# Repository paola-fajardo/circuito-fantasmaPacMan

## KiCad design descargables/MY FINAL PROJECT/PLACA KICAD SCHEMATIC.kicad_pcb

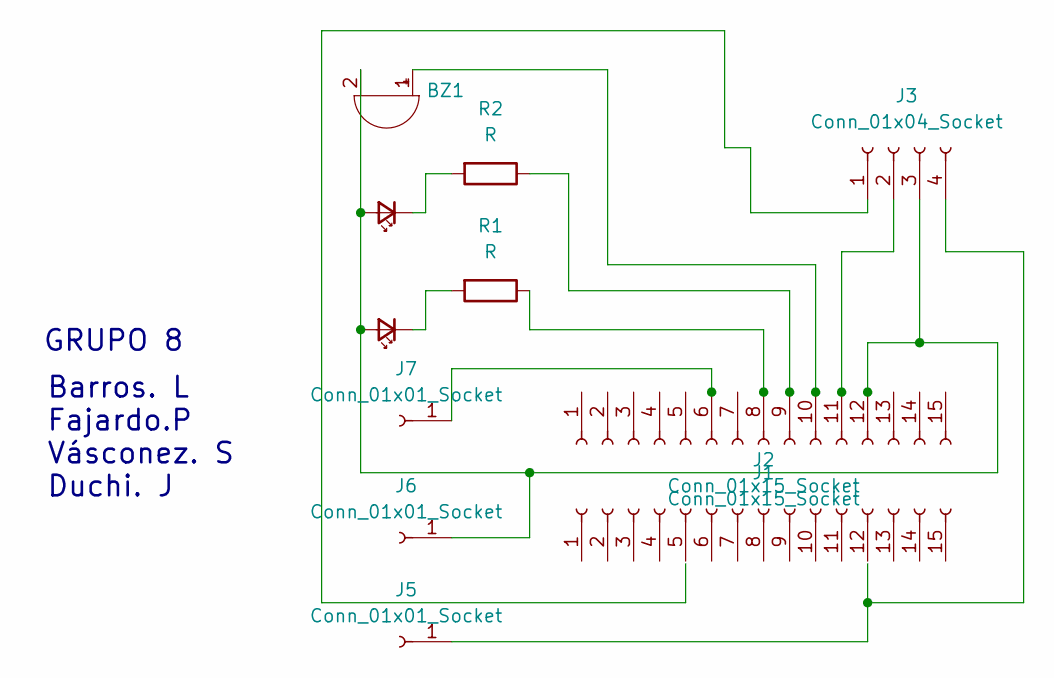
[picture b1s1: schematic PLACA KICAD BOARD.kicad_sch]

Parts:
BZ1: Buzzer; Buzzer_12x9.5RM7.6
D4, D5: LED_Small; LED_D5.0mm
J1, J2: Conn_01x15_Socket; PinSocket_1x15_P2.54mm_Vertical
J3: Conn_01x04_Socket; PinSocket_1x04_P2.54mm_Vertical
J5, J6, J7: Conn_01x01_Socket; PinSocket_1x01_P2.54mm_Vertical
R1, R2: R; R_Axial_DIN0207_L6.3mm_D2.5mm_P10.16mm_Horizontal

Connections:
unnamed: BZ1.1 (+), J1.10
unnamed: BZ1.2 (-), D4.2 (A), D5.2 (A), J1.12, J3.3, J6.1 (Pin_1_1)
unnamed: D4.1 (K), R1.2
unnamed: D5.1 (K), R2.2
unnamed: J1.6, J7.1 (Pin_1_1)
unnamed: J1.8, R1.1
unnamed: J1.9, R2.1
unnamed: J1.11, J3.2
unnamed: J3.4, J5.1 (Pin_1_1)

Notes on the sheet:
GRUPO 8
Barros. L Fajardo.P Vásconez. S Duchi. J

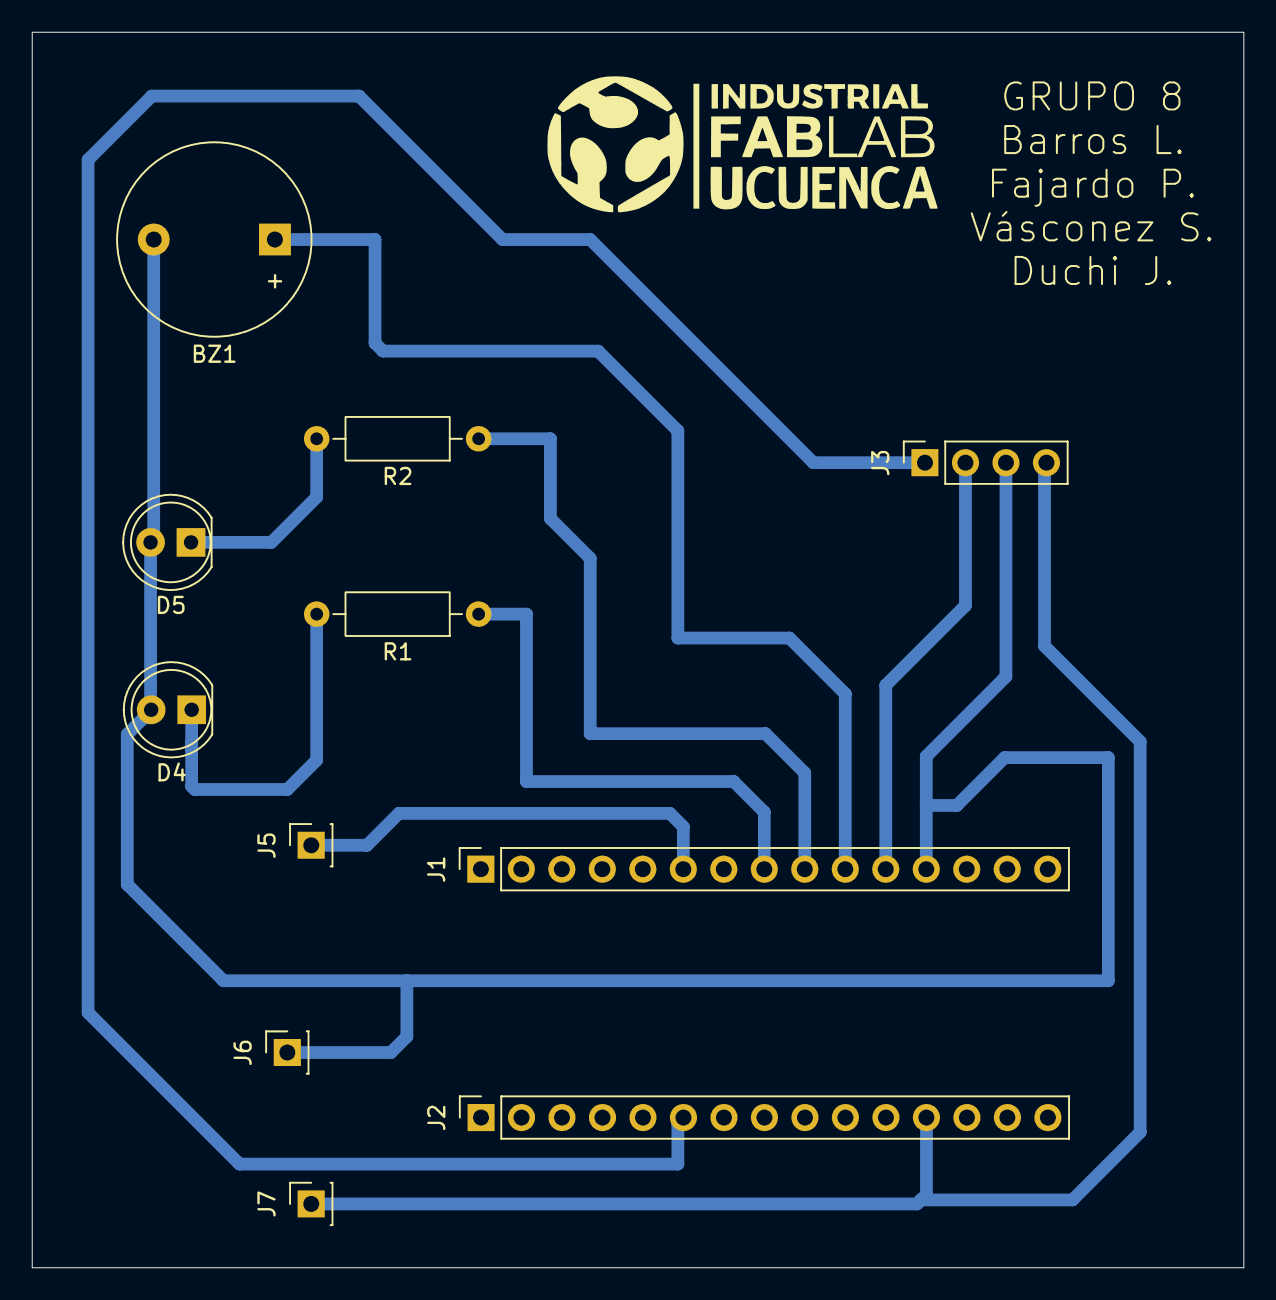
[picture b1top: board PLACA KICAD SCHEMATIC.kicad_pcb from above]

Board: 2 copper layers, 76.0 x 77.5 mm, 11 parts (0 on the bottom side), 9 nets.

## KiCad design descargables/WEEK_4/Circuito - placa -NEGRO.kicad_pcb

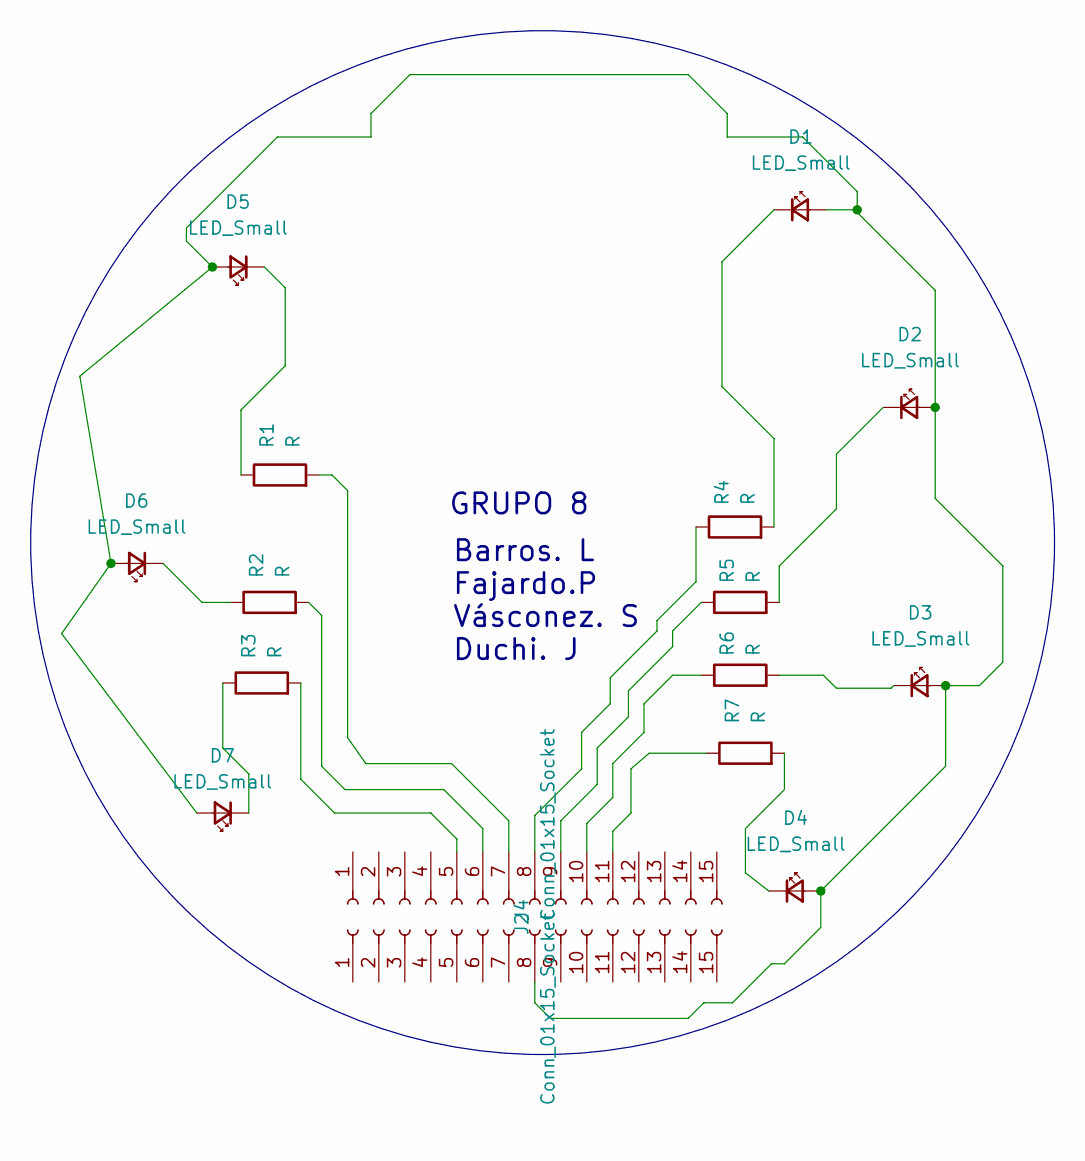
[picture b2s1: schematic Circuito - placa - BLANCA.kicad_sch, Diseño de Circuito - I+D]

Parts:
D1, D2, D3, D4, D5, D6, D7: LED_Small; LED_D5.0mm
J2, J4: Conn_01x15_Socket; PinSocket_1x15_P2.54mm_Vertical
R1, R2, R3, R4, R5, R6, R7: R; R_Axial_DIN0207_L6.3mm_D2.5mm_P10.16mm_Horizontal

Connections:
unnamed: D1.2 (A), D2.2 (A), D3.2 (A), D4.2 (A), D5.2 (A), D6.2 (A), D7.2 (A), J4.8 (Pin_8_8)
unnamed: D1.1 (K), R4.2
unnamed: D2.1 (K), R5.2
unnamed: D3.1 (K), R6.2
unnamed: D4.1 (K), R7.2
unnamed: D5.1 (K), R1.1
unnamed: D6.1 (K), R2.1
unnamed: D7.1 (K), R3.1
unnamed: J2.5, R3.2
unnamed: J2.6, R2.2
unnamed: J2.7, R1.2
unnamed: J2.8, R4.1
unnamed: J2.9, R5.1
unnamed: J2.10, R6.1
unnamed: J2.11, R7.1

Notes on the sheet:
GRUPO 8
Barros. L Fajardo.P Vásconez. S Duchi. J

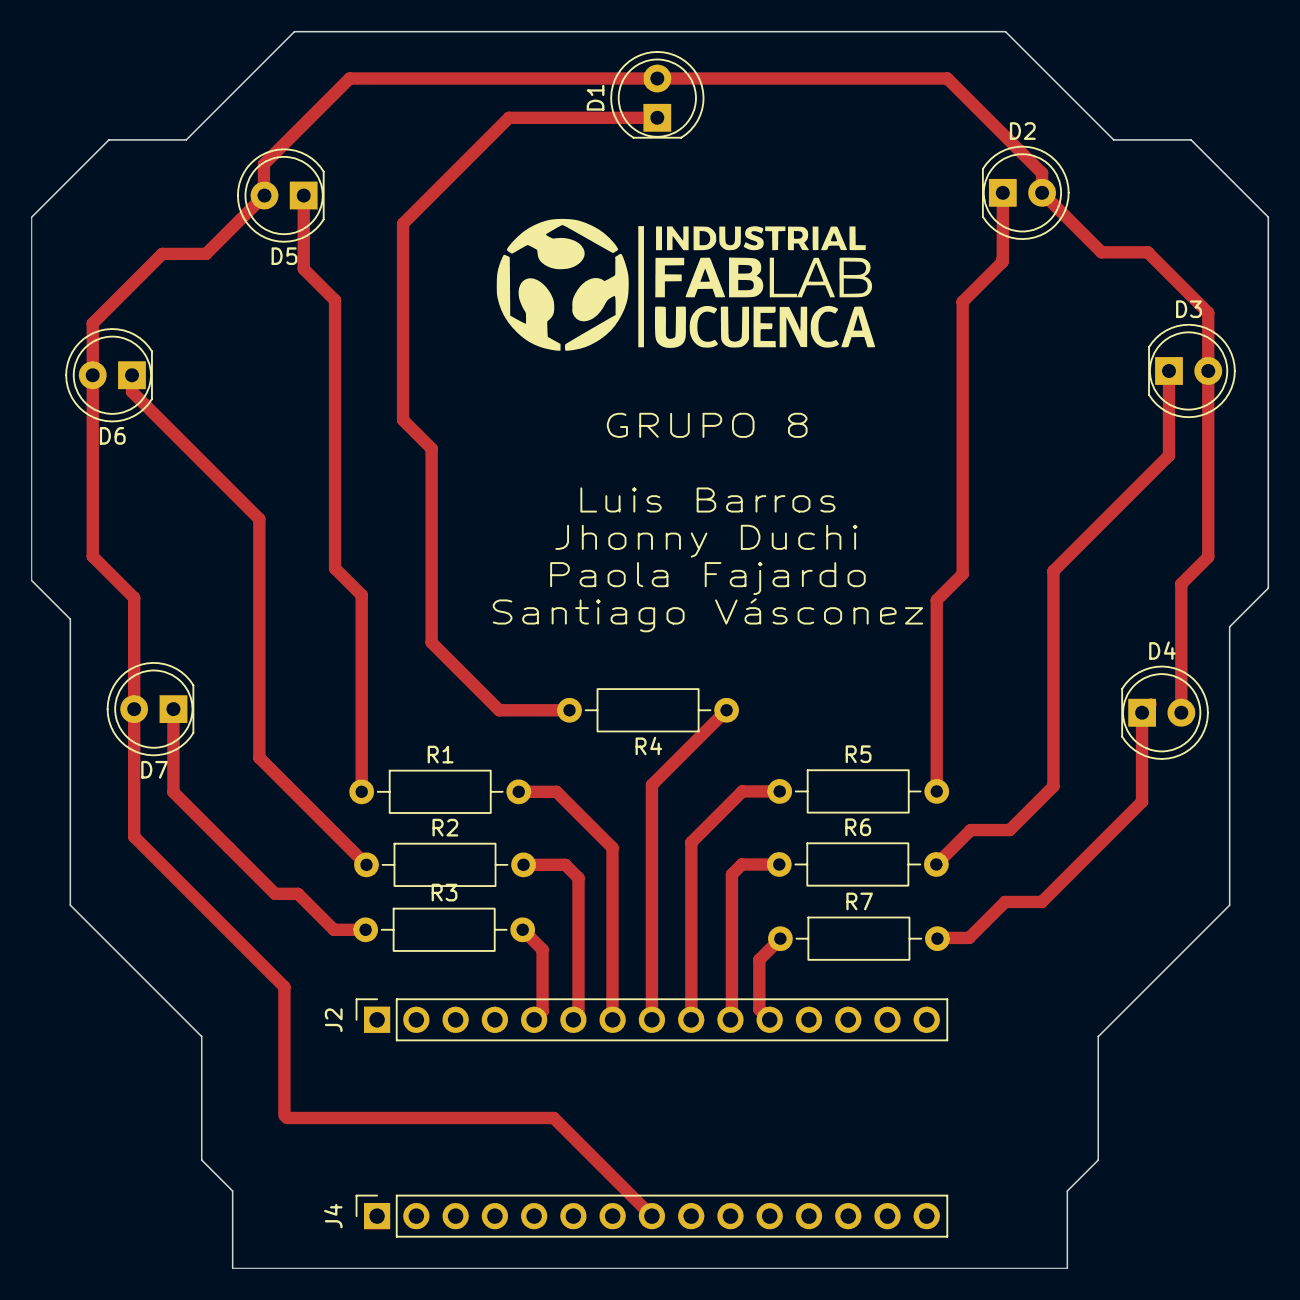
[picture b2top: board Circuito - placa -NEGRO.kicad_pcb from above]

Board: 2 copper layers, 80.0 x 80.0 mm, 16 parts (0 on the bottom side), 15 nets.

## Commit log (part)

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2026-06-12 Mi primer commit - Grupo 8
2026-06-12 Crear redireccion limpia a Semana 4
2026-06-12 Nuevos cambios en el index de prueba
2026-06-12 Actualizacion completa: Pagina web adaptada y corregida para servidor
